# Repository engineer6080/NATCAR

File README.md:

# NATCAR
UC Davis Natcar project. Autonomous track navigation using PID control scheme.

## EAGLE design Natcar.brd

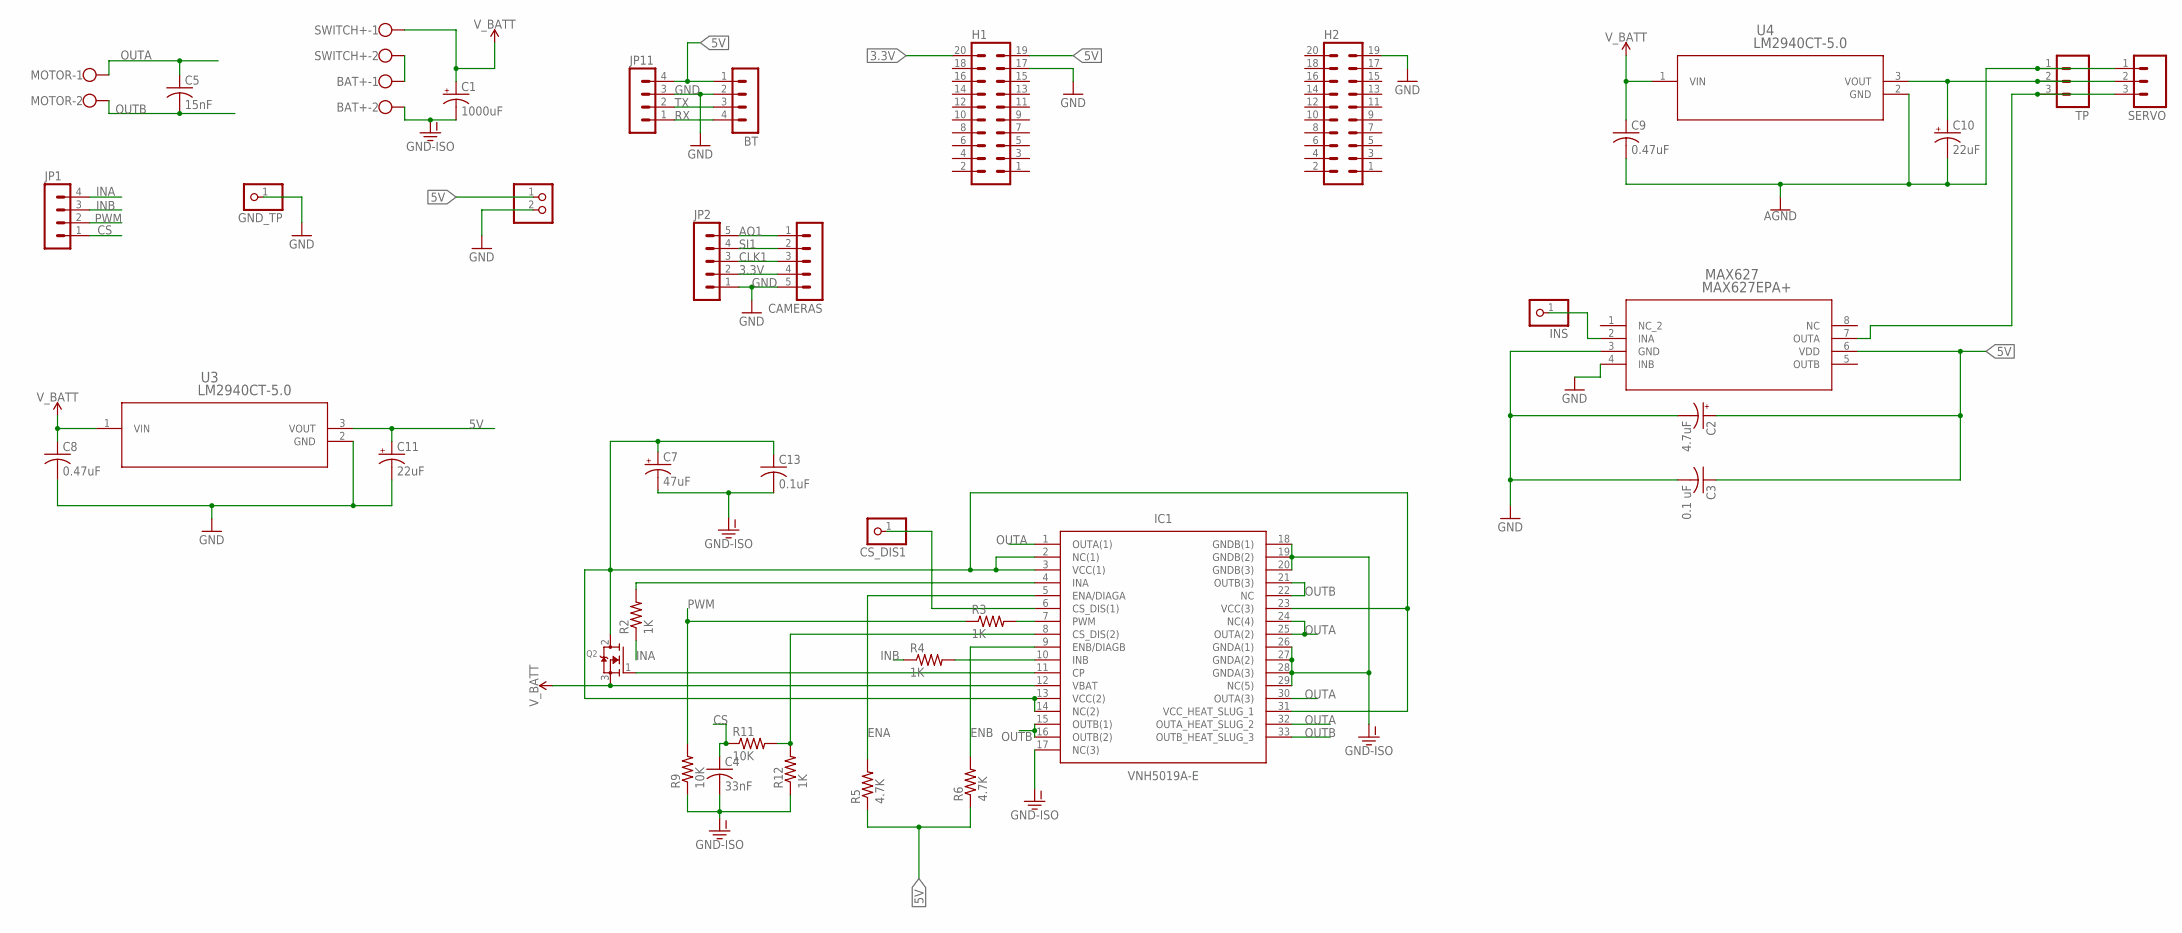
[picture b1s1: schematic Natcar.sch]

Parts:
BAT+: W237-102
BT: MA04-1
C1: 1000uF; E5-10,5
C2: 4.7uF; E2-5
C3: 0.1 uF; C025-030X050
C4: 33nF; C025-030X050
C5: 15nF; C025-030X050
C7: 47uF; E2,5-5
C8, C9: 0.47uF; C025-030X050
C10, C11: 22uF; E2,5-5
C13: 0.1uF; C025-030X050
CAMERAS: MA05-1
CS_DIS1: PINHD-1X1; 1X01
GND_TP: PINHD-1X1; 1X01
H1, H2: MA10-2
IC1: VNH5019A-E; VNH5019A-E_1
INS: PINHD-1X1; 1X01
JP1, JP11: MA04-1
JP2: MA05-1
JP12: PINHD-1X2; 1X02
MAX627: MAX627EPA+; 21-0043D_8
MOTOR: W237-102
Q2: MOSFET-NGDS_TO220V; TO220V
R2, R3, R4, R12: 1K; 0309/10
R5, R6: 4.7K; 0309/10
R9, R11: 10K; 0309/10
SERVO: MA03; 03P
SWITCH+: W237-102
TP: MA03; 03P
U3, U4: LM2940CT-5.0; T03B

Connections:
3.3V: CAMERAS.4, H1.20, JP2.2
5V: BT.1, C2.+, C3.1, C11.+, H1.19, JP11.4, JP12.1, MAX627.6 (VDD), R5.1, R6.1, U3.3 (VOUT)
AGND: C9.2, C10.-, SERVO.1, TP.1, U4.2 (GND)
AO1: CAMERAS.1, JP2.5
CLK1: CAMERAS.3, JP2.3
CS: C4.1, JP1.1, R11.1
ENA: IC1.5 (ENA/DIAGA), R5.2
ENB: IC1.9 (ENB/DIAGB), R6.2
GND: BT.2, C2.-, C3.2, C8.2, C11.-, CAMERAS.5, GND_TP.1, H1.17, H2.19, JP2.1, JP11.3, JP12.2, MAX627.3 (GND), MAX627.4 (INB), U3.2 (GND)
GND-ISO: BAT+.2, C1.-, C4.2, C7.-, C13.2, IC1.17 (NC(3)), IC1.18 (GNDB(1)), IC1.19 (GNDB(2)), IC1.20 (GNDB(3)), IC1.26 (GNDA(1)), IC1.27 (GNDA(2)), IC1.28 (GNDA(3)), IC1.29 (NC(5)), R9.1, R12.1
INA: JP1.4, R2.1
INB: JP1.3, R4.1
unnamed: BAT+.1, SWITCH+.2
unnamed: IC1.11 (CP), Q2.1 (G)
unnamed: IC1.10 (INB), R4.2
unnamed: C7.+, C13.1, IC1.2 (NC(1)), IC1.3 (VCC(1)), IC1.13 (VCC(2)), IC1.14 (NC(2)), IC1.23 (VCC(3)), IC1.31 (VCC_HEAT_SLUG_1), Q2.2 (D)
unnamed: IC1.4 (INA), R2.2
unnamed: CS_DIS1.1, IC1.6 (CS_DIS(1))
unnamed: IC1.7 (PWM), R3.2
unnamed: INS.1, MAX627.2 (INA)
unnamed: MAX627.7 (OUTA), SERVO.3, TP.3
unnamed: IC1.8 (CS_DIS(2)), R11.2, R12.2
unnamed: C10.+, SERVO.2, TP.2, U4.3 (VOUT)
OUTA: C5.1, IC1.1 (OUTA(1)), IC1.24 (NC(4)), IC1.25 (OUTA(2)), IC1.30 (OUTA(3)), IC1.32 (OUTA_HEAT_SLUG_2), MOTOR.1
OUTB: C5.2, IC1.15 (OUTB(1)), IC1.16 (OUTB(2)), IC1.21 (OUTB(3)), IC1.22 (NC), IC1.33 (OUTB_HEAT_SLUG_3), MOTOR.2
PWM: JP1.2, R3.1, R9.2
RX: BT.4, JP11.1
SI1: CAMERAS.2, JP2.4
TX: BT.3, JP11.2
V_BATT: C1.+, C8.1, C9.1, IC1.12 (VBAT), Q2.3 (S), SWITCH+.1, U3.1 (VIN), U4.1 (VIN)

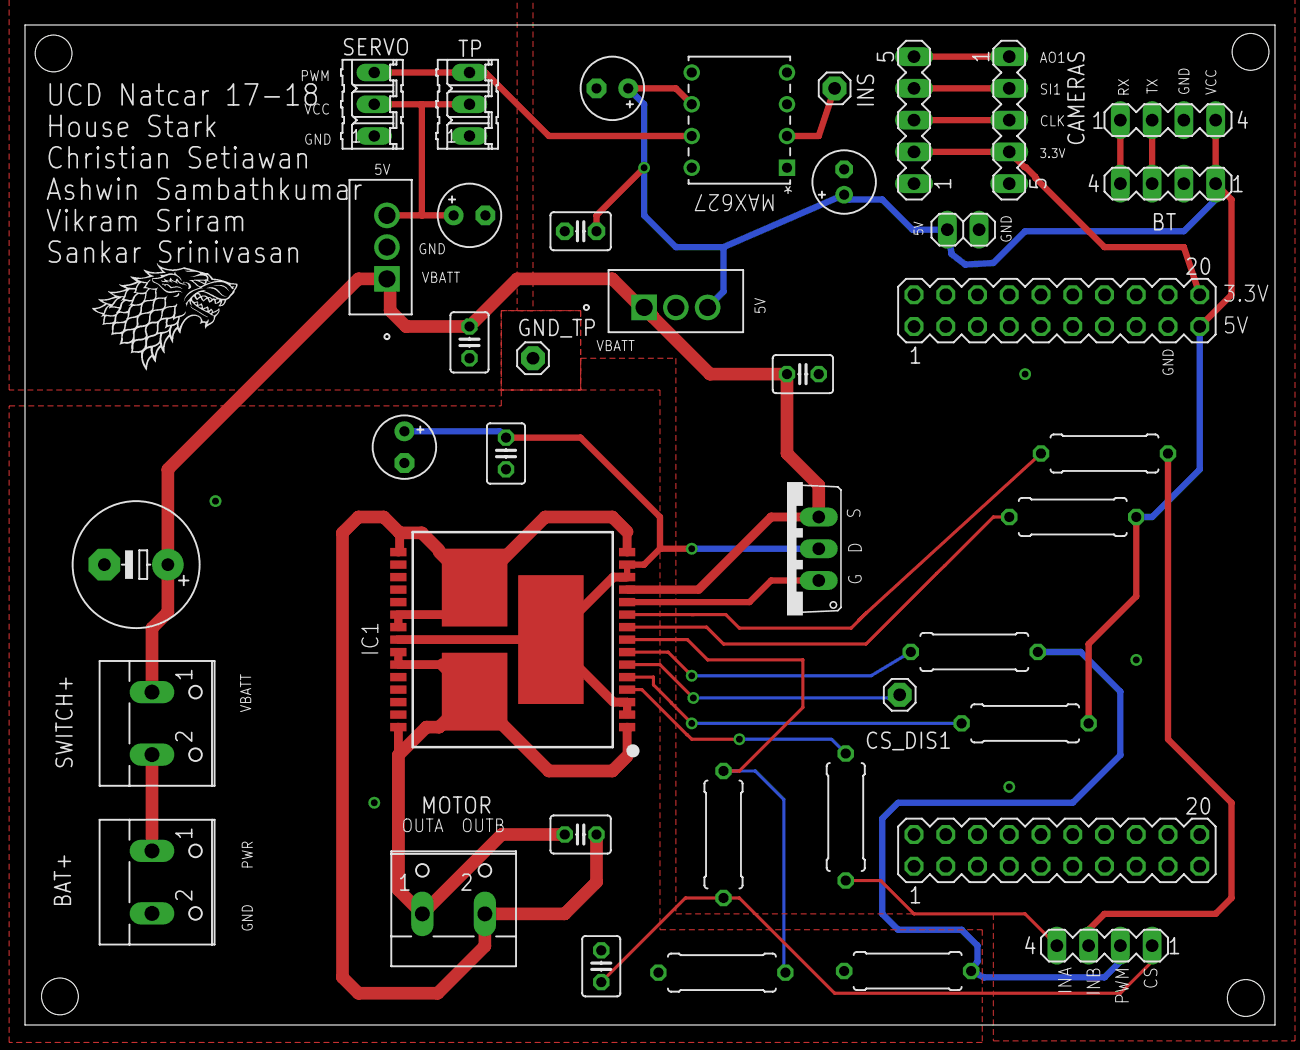
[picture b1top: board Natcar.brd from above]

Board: 2 copper layers, 100.0 x 80.0 mm, 40 parts (0 on the bottom side), 30 nets.

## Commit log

2019-12-31 migrating

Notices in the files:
parts and their libraries:
SparkFun-PowerSymbols: Licensing: Creative Commons ShareAlike 4.0 International - https://creativecommons.org/licenses/by-sa/4.0
